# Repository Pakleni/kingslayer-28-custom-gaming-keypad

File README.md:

# Kingslayer 28
*Fully custom 28 key gaming keypad*

## Images

### Keyboard Layout

### Plate

### PCB

## Features
* Per-Key RGB
* South Facing LED
* Hot-Swap Sockets
* Custom Plate
* USB-C
* 5-pin Sockets
* Plate Mount & PCB Screw-in Stabilizer support
* Top mount design
* QMK support
* Wrist Rest with magnetic attachment mechanism
* 5 degree positive tilt

## Used
* http://www.keyboard-layout-editor.com
* http://builder.swillkb.com
* https://librecad.org
* https://www.kicad.org

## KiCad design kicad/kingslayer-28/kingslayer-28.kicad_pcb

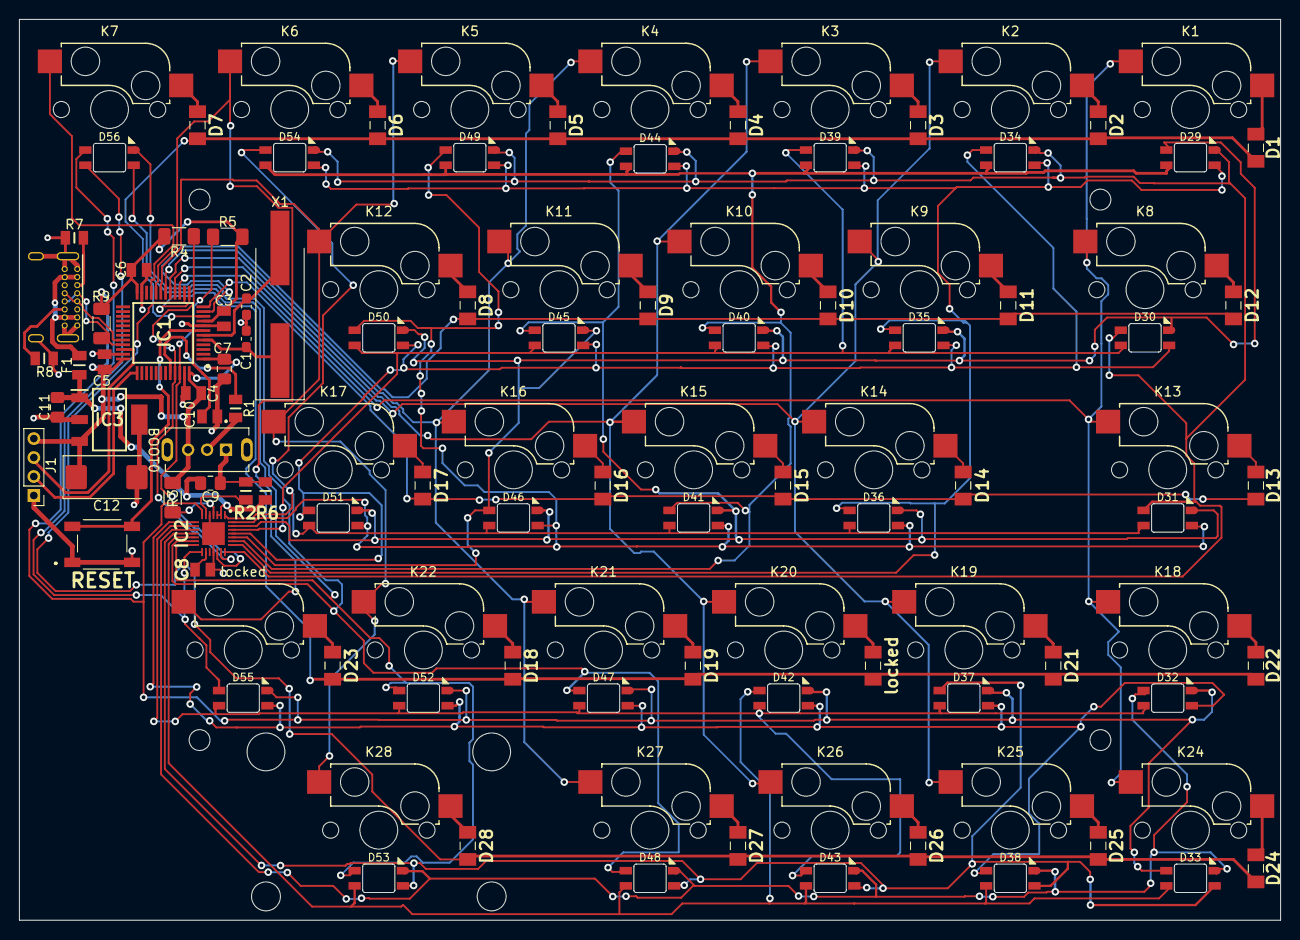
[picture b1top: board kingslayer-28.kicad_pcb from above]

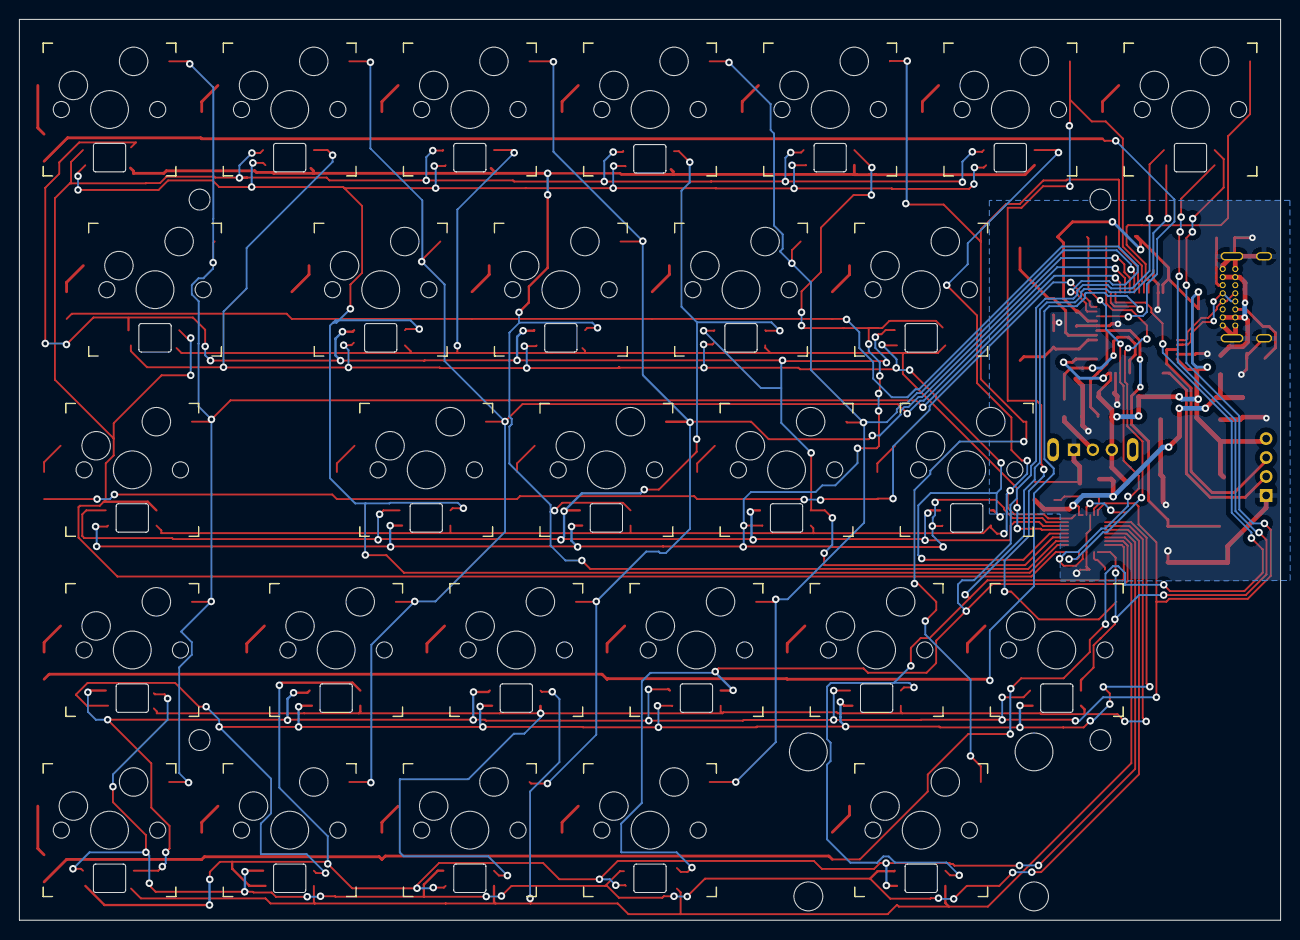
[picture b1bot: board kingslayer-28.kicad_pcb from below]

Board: 2 copper layers, 133.0 x 95.0 mm, 119 parts (33 on the bottom side), 78 nets.

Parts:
C1, C2: 22p; C_0603_1608Metric_Pad1.08x0.95mm_HandSolder
C3, C4, C5, C6, C10: 100n; CAPC2012X94N
C7: 4.7u; C_0805_2012Metric_Pad1.18x1.45mm_HandSolder
C8: 0.1u; CAPC2012X94N
C9: 1u; C_0805_2012Metric_Pad1.18x1.45mm_HandSolder
C11: 0.47u; C_0805_2012Metric_Pad1.18x1.45mm_HandSolder
C12: 33u; CP_EIA-7343-31_Kemet-D_Pad2.25x2.55mm_HandSolder
D1, D2, D3, D4, D5, D6, D7, D8, D9, D10, D11, D12, D13, D14, D15, D16, D17, D18, D19, D21, D22, D23, D24, D25, D26, D27, D28: 1N4148W RHG; 1N4148WRHG
D29, D30, D31, D32, D33, D34, D35, D36, D37, D38, D39, D40, D41, D42, D43, D44, D45, D46, D47, D48, D49, D50, D51, D52, D53, D54, D55, D56: 6028_LED; LED_RGB_SMD_6028_2.8x3.5mm_Square
F1: 0ZCK0050FF2E; FUSC2214X125N
H1: Stabilizer Mount; Stabilizer_MX_2u
H2, H3, H4, H5: MountingHole; MountingHole_2.2mm_M2_ISO7380
IC1: STM32F303CCT7; QFP50P900X900X160-48N
IC2: IS31FL3731-QFLS2-TR; QFN40P400X400X80-29N
IC3: LM3940IMP-3.3_NOPB; SOT230P700X180-4N
J1: Conn_01x04_Pin; PinHeader_1x04_P2.00mm_Vertical
K1, K2, K3, K4, K5, K6, K7, K8, K9, K10, K11, K12, K13, K14, K15, K16, K17, K18, K19, K20, K21, K22, K24, K25, K26, K27, K28: KEYSW; Kailh_socket_MX
R1: 10k; RESC2012X65N
R2: 20k; RESC2012X60N
R3, R4, R5: 4.7k; R_1206_3216Metric_Pad1.30x1.75mm_HandSolder
R6: 100k; RESC2012X65N
R7, R8: 5.1k; RESC2012X60N
R9: 1k5; R_1206_3216Metric_Pad1.30x1.75mm_HandSolder
S1: TL3342F260QG
SW1: SS12D07; SW_SS12D07VG4
USB1: 12401598E4#2A; USB_C_GCT_USB4085
X1: IC21008.000M30.0EE1B; Crystal_SMD_HC49-SD_HandSoldering
locked: 1N4148W RHG; 1N4148WRHG
locked#2: KEYSW; Kailh_socket_MX

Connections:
+3V3: C3.1, C4.1, C5.1, C6.1, C7.1, C12.1, IC1.1 (VBAT), IC1.9 (VDDA), IC1.24 (VDD_1), IC1.36 (VDD_2), IC1.48 (VDD_3), IC3.3 (OUT), J1.4, R3.1, R4.1, R5.1, R9.1, SW1.3 (C)
+5V: C9.1, C11.1, F1.2, IC2.2 (VCC), IC2.3 (SDB), IC3.1 (IN), R6.1
/RGB/scl: IC1.45 (PB8), IC2.20 (SCL), R4.2
/RGB/sda: IC1.46 (PB9), IC2.19 (SDA), R5.2
GND: C1.2, C2.2, C3.2, C4.2, C5.2, C6.2, C7.2, C8.2, C9.2, C10.1, C11.2, C12.2, IC1.8 (VSSA/VREF-), IC1.23 (VSS_1), IC1.35 (VSS_2), IC1.47 (VSS_3), IC2.5 (GND), IC2.18 (AD), IC2.29 (PAD), IC3.2 (GND_1), IC3.4 (GND_2), J1.1, R2.2, R6.2, R7.2, R8.2, S1.1, S1.2, SW1.1 (A), USB1.A1 (GND), USB1.A12 (GND), USB1.B1 (GND), USB1.B12 (GND), USB1.S1 (Shell1)
unnamed: D1.2, K1.2
unnamed: D2.2, K2.2
unnamed: D3.2, K3.2
unnamed: D4.2, K4.2
unnamed: D5.2, K5.2
unnamed: D6.2, K6.2
unnamed: D7.2, K7.2
unnamed: D8.2, K12.2
unnamed: D9.2, K11.2
unnamed: D10.2, K10.2
unnamed: D11.2, K9.2
unnamed: D12.2, K8.2
unnamed: D13.2, K13.2
unnamed: D14.2, K14.2
unnamed: D15.2, K15.2
unnamed: D16.2, K16.2
unnamed: D17.2, K17.2
unnamed: D18.2, K22.2
unnamed: D19.2, K21.2
unnamed: K20.2, locked.2
unnamed: D21.2, K19.2
unnamed: D22.2, K18.2
unnamed: D23.2, locked#2.2
unnamed: D24.2, K24.2
unnamed: D25.2, K25.2
unnamed: D26.2, K26.2
unnamed: D27.2, K27.2
unnamed: D28.2, K28.2
unnamed: F1.1, USB1.A4 (VBUS), USB1.A9 (VBUS), USB1.B4 (VBUS), USB1.B9 (VBUS)
unnamed: R1.1, SW1.2 (B)
unnamed: R7.1, USB1.A5 (CC1)
unnamed: R8.1, USB1.B5 (CC2)
boot0: IC1.44 (BOOT0), R1.2
c_filt: C8.1, IC2.16 (C_FILT)
ca1: D29.4 (RK), D30.2 (A), D31.2 (A), D34.4 (RK), D39.4 (RK), D44.4 (RK), D49.4 (RK), D54.4 (RK), IC2.21 (CA1)
ca2: D29.3 (GK), D34.3 (GK), D35.2 (A), D36.2 (A), D39.3 (GK), D44.3 (GK), D49.3 (GK), D54.3 (GK), IC2.22 (CA2)
ca3: D29.1 (BK), D34.1 (BK), D39.1 (BK), D40.2 (A), D41.2 (A), D44.1 (BK), D49.1 (BK), D54.1 (BK), IC2.23 (CA3)
ca4: D29.2 (A), D30.4 (RK), D35.4 (RK), D40.4 (RK), D45.4 (RK), D46.2 (A), D50.4 (RK), IC2.24 (CA4)
ca5: D30.3 (GK), D34.2 (A), D35.3 (GK), D40.3 (GK), D45.3 (GK), D50.3 (GK), D51.2 (A), IC2.25 (CA5)
ca6: D30.1 (BK), D35.1 (BK), D39.2 (A), D40.1 (BK), D45.1 (BK), D50.1 (BK), IC2.26 (CA6)
ca7: D31.4 (RK), D36.4 (RK), D41.4 (RK), D44.2 (A), D45.2 (A), D46.4 (RK), D51.4 (RK), IC2.27 (CA7)
ca8: D31.3 (GK), D36.3 (GK), D41.3 (GK), D46.3 (GK), D49.2 (A), D50.2 (A), D51.3 (GK), IC2.28 (CA8)
ca9: D31.1 (BK), D36.1 (BK), D41.1 (BK), D46.1 (BK), D51.1 (BK), D54.2 (A), IC2.1 (CA9)
cb1: D32.4 (RK), D33.2 (A), D37.4 (RK), D42.4 (RK), D47.4 (RK), D52.4 (RK), D55.4 (RK), D56.2 (A), IC2.7 (CB1)
cb2: D32.3 (GK), D37.3 (GK), D38.2 (A), D42.3 (GK), D47.3 (GK), D52.3 (GK), D55.3 (GK), IC2.8 (CB2)
cb3: D32.1 (BK), D37.1 (BK), D42.1 (BK), D43.2 (A), D47.1 (BK), D52.1 (BK), D55.1 (BK), IC2.9 (CB3)
cb4: D32.2 (A), D33.4 (RK), D38.4 (RK), D43.4 (RK), D48.4 (RK), D53.4 (RK), IC2.10 (CB4)
cb5: D33.3 (GK), D37.2 (A), D38.3 (GK), D43.3 (GK), D48.3 (GK), D53.3 (GK), IC2.11 (CB5)
cb6: D33.1 (BK), D38.1 (BK), D42.2 (A), D43.1 (BK), D48.1 (BK), D53.1 (BK), IC2.12 (CB6)
cb7: D47.2 (A), D48.2 (A), D56.4 (RK), IC2.13 (CB7)
cb8: D52.2 (A), D53.2 (A), D56.3 (GK), IC2.14 (CB8)
cb9: D55.2 (A), D56.1 (BK), IC2.15 (CB9)
col0: IC1.15 (PA5), K1.1, K8.1, K13.1, K18.1, K24.1
col1: IC1.16 (PA6), K2.1, K9.1, K14.1, K19.1, K25.1
col2: IC1.17 (PA7), K3.1, K10.1, K15.1, K20.1, K26.1
col3: IC1.18 (PB0), K4.1, K11.1, K16.1, K21.1, K27.1
col4: IC1.19 (PB1), K5.1, K12.1, K17.1, K22.1, K28.1
col5: IC1.20 (PB2), K6.1, locked#2.1
col6: IC1.21 (PB10), K7.1
d+: IC1.33 (PA12), R9.2, USB1.A6 (D+), USB1.B6 (D+)
d-: IC1.32 (PA11), USB1.A7 (D-), USB1.B7 (D-)
intb: IC2.4 (INTB), R3.2
nrst: C10.2, IC1.7 (NRST), S1.3, S1.4
r_ext: IC2.6 (R_EXT), R2.1
row0: D1.1, D2.1, D3.1, D4.1, D5.1, D6.1, D7.1, IC1.10 (PA0)
row1: D8.1, D9.1, D10.1, D11.1, D12.1, IC1.11 (PA1)
row2: D13.1, D14.1, D15.1, D16.1, D17.1, IC1.12 (PA2)
row3: D18.1, D19.1, D21.1, D22.1, D23.1, IC1.13 (PA3), locked.1
row4: D24.1, D25.1, D26.1, D27.1, D28.1, IC1.14 (PA4)
swclk: IC1.37 (PA14), J1.2
swdio: IC1.34 (PA13), J1.3
xtal1: C1.1, IC1.5 (PF0/OSC_IN), X1.1
xtal2: C2.1, IC1.6 (PF1/OSC_OUT), X1.2

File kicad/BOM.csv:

Number,Name,Value,Amount,Link
1,Hot-swap Sockets,DUROCK Transparent MX,28,https://www.aliexpress.com/item/1005005090520759.html
2,RGB Diodes,SMD 3528/6028 RGB LED,28,https://www.aliexpress.com/item/32834931333.html
3,Switch Diodes,1N4148W RHG,28,https://eu.mouser.com/ProductDetail/821-1N4148WRHG
4,Microcontroller,STM32F303CCT7,1,https://eu.mouser.com/ProductDetail/STMicroelectronics/STM32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
5,USB C connector,USB4085-GF-A,1,https://eu.mouser.com/ProductDetail/640-USB4085-GF-A
6,Reset Switch,TL3342F260QG,1,https://eu.mouser.com/ProductDetail/612-TL3342F260QG
7,LED Driver,IS31FL3731-QFLS2-TR,1,https://eu.mouser.com/ProductDetail/870-31FL3731-QFLS2TR
8,Fuse,0ZCK0050FF2E,1,https://eu.mouser.com/ProductDetail/530-0ZCK0050FF2E
9,Crystal,IC21008.000M30.0EE1B,1,https://www.mgelectronic.rs/quarze-kristal-smd-8-mhz
10,Voltage Regulator,"LM 3940 IMP-3,3",1,https://www.mgelectronic.rs/integrisano-kolo-lm-3940-imp-33
11,Header,DS1025-01-1*4P8BV1-B,1,https://www.mgelectronic.rs/1-1154
12,SPDT Switch,SS12D07,1,https://kelco.rs/katalog/detalji.php?ID=18042
13,Capacitor,22p,2,https://kelco.rs/katalog/detalji.php?ID=12900
14,Capacitor,0.1u/100n,6,https://eu.mouser.com/ProductDetail/581-08053C104K
15,Capacitor,0.47u/470n,1,https://eu.mouser.com/ProductDetail/187-CL21B474KOFNNNE
16,Capacitor,1u,1,https://kelco.rs/katalog/detalji.php?ID=12933
17,Capacitor,4.7u,1,https://kelco.rs/katalog/detalji.php?ID=20226
18,Capacitor,33u,1,https://kelco.rs/katalog/detalji.php?ID=10224
19,Resistor,1.5k,1,https://kelco.rs/katalog/detalji.php?ID=9477
20,Resistor,4.7k,3,https://kelco.rs/katalog/detalji.php?ID=9485
21,Resistor,5.1k,2,https://eu.mouser.com/ProductDetail/652-CR0805FX-5101ELF
22,Resistor,10k,1,https://eu.mouser.com/ProductDetail/708-RMCF0805JT10K0
23,Resistor,20k,1,https://eu.mouser.com/ProductDetail/652-CR0805JW-203ELF
24,Resistor,100k,1,https://eu.mouser.com/ProductDetail/708-RMCF0805JT100K

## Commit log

2023-09-16 add images
2023-09-26 Day 1
2023-09-26 Setting up microcontroller
2023-09-27 Add RGB controller
2023-09-27 tidy up the schematic
2023-09-27 add RGB matrix
2023-09-27 RGB matrix 2
2023-09-28 USB C
2023-09-28 connect rgb
2023-09-30 progress?
2023-10-01 MCU done...
2023-10-01 done I guess
2023-10-01 add info
2023-10-01 oops
2023-10-01 add PCB images
2023-10-02 Addressed some comments
2023-10-02 update pics
2023-10-05 Update after watching phil
2023-10-06 ground shield
2023-10-06 ERC check
2023-10-12 assign some footprints
2023-10-12 add TODO
2023-10-12 update mounting holes
2023-10-12 header, switch, oscillator
2023-10-19 footprint mapping
2023-10-20 Add fuse because of tantalum cap
2023-12-10 finish footprint picking
2023-12-10 placed switches, switch diodes and mounting holes
2023-12-11 initial placement
2023-12-11 swap mcu location
2023-12-11 routing in progress
2024-01-05 revert footprints, finalize placement
2024-01-05 backup
2024-01-06 finish routing?
2024-01-06 added usb c 3d model
2024-01-06 revert model change
2024-01-06 3d model
2024-01-06 add 3d design
2024-01-07 Started DRC
2024-01-07 finish DRC
2024-01-07 update pictures
2024-01-09 Add BOM
2024-01-22 update top
2024-02-11 found first error, need to redo pics and manufacturing
2024-02-12 add VIA
2024-02-12 ground loop
2024-02-18 fix RGB
2024-02-18 generate new manufacturing files
2024-06-09 add print
2024-06-16 new designs
2024-07-02 revert models
2026-06-02 Update README with new images and section titles
